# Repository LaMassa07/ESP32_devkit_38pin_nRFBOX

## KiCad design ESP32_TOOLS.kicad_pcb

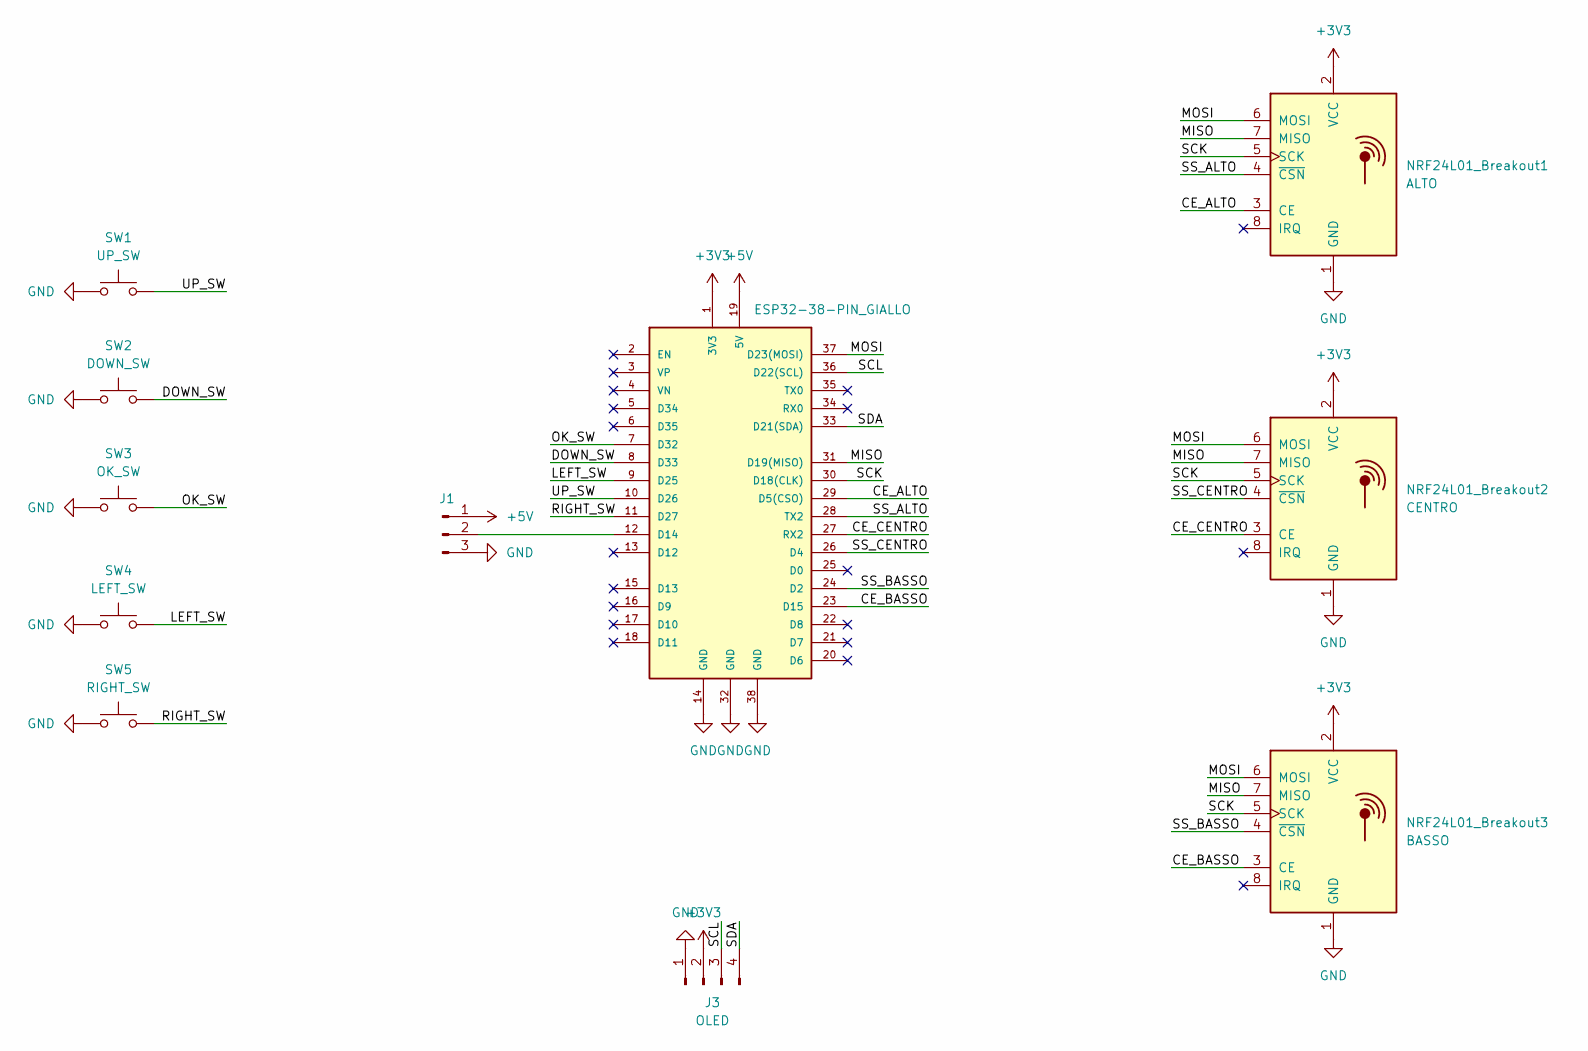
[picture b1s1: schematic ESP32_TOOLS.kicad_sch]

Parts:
J1: LED; PinHeader_1x03_P2.54mm_Vertical
J3: OLED; 128x64OLED
NRF24L01_Breakout1: ALTO; nRF24L01_PA_LNA
NRF24L01_Breakout2: CENTRO; nRF24L01_PA_LNA
NRF24L01_Breakout3: BASSO; nRF24L01_PA_LNA
S1: ESP32-38-PIN_GIALLO; ESP32-38-PIN; PARTREV N/A
SW1: UP_SW; SW_PUSH_6mm_H9.5mm
SW2: DOWN_SW; SW_PUSH_6mm_H9.5mm
SW3: OK_SW; SW_PUSH_6mm_H9.5mm
SW4: LEFT_SW; SW_PUSH_6mm_H9.5mm
SW5: RIGHT_SW; SW_PUSH_6mm_H9.5mm

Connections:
+3V3: J3.2, NRF24L01_Breakout1.2 (VCC), NRF24L01_Breakout2.2 (VCC), NRF24L01_Breakout3.2 (VCC), S1.1 (3V3)
+5V: J1.1, S1.19 (5V)
/CE_ALTO: NRF24L01_Breakout1.3 (CE), S1.29 (D5(CSO))
/CE_BASSO: NRF24L01_Breakout3.3 (CE), S1.23 (D15)
/CE_CENTRO: NRF24L01_Breakout2.3 (CE), S1.27 (RX2)
/DOWN_SW: S1.8 (D33), SW2.2
/LEFT_SW: S1.9 (D25), SW4.2
/MISO: NRF24L01_Breakout1.7 (MISO), NRF24L01_Breakout2.7 (MISO), NRF24L01_Breakout3.7 (MISO), S1.31 (D19(MISO))
/MOSI: NRF24L01_Breakout1.6 (MOSI), NRF24L01_Breakout2.6 (MOSI), NRF24L01_Breakout3.6 (MOSI), S1.37 (D23(MOSI))
/OK_SW: S1.7 (D32), SW3.2
/RIGHT_SW: S1.11 (D27), SW5.2
/SCK: NRF24L01_Breakout1.5 (SCK), NRF24L01_Breakout2.5 (SCK), NRF24L01_Breakout3.5 (SCK), S1.30 (D18(CLK))
/SCL: J3.3, S1.36 (D22(SCL))
/SDA: J3.4, S1.33 (D21(SDA))
/SS_ALTO: NRF24L01_Breakout1.4 (~CSN), S1.28 (TX2)
/SS_BASSO: NRF24L01_Breakout3.4 (~CSN), S1.24 (D2)
/SS_CENTRO: NRF24L01_Breakout2.4 (~CSN), S1.26 (D4)
/UP_SW: S1.10 (D26), SW1.2
GND: J1.3, J3.1, NRF24L01_Breakout1.1 (GND), NRF24L01_Breakout2.1 (GND), NRF24L01_Breakout3.1 (GND), S1.14 (GND), S1.32 (GND), S1.38 (GND), SW1.1, SW2.1, SW3.1, SW4.1, SW5.1
unnamed: J1.2, S1.12 (D14)

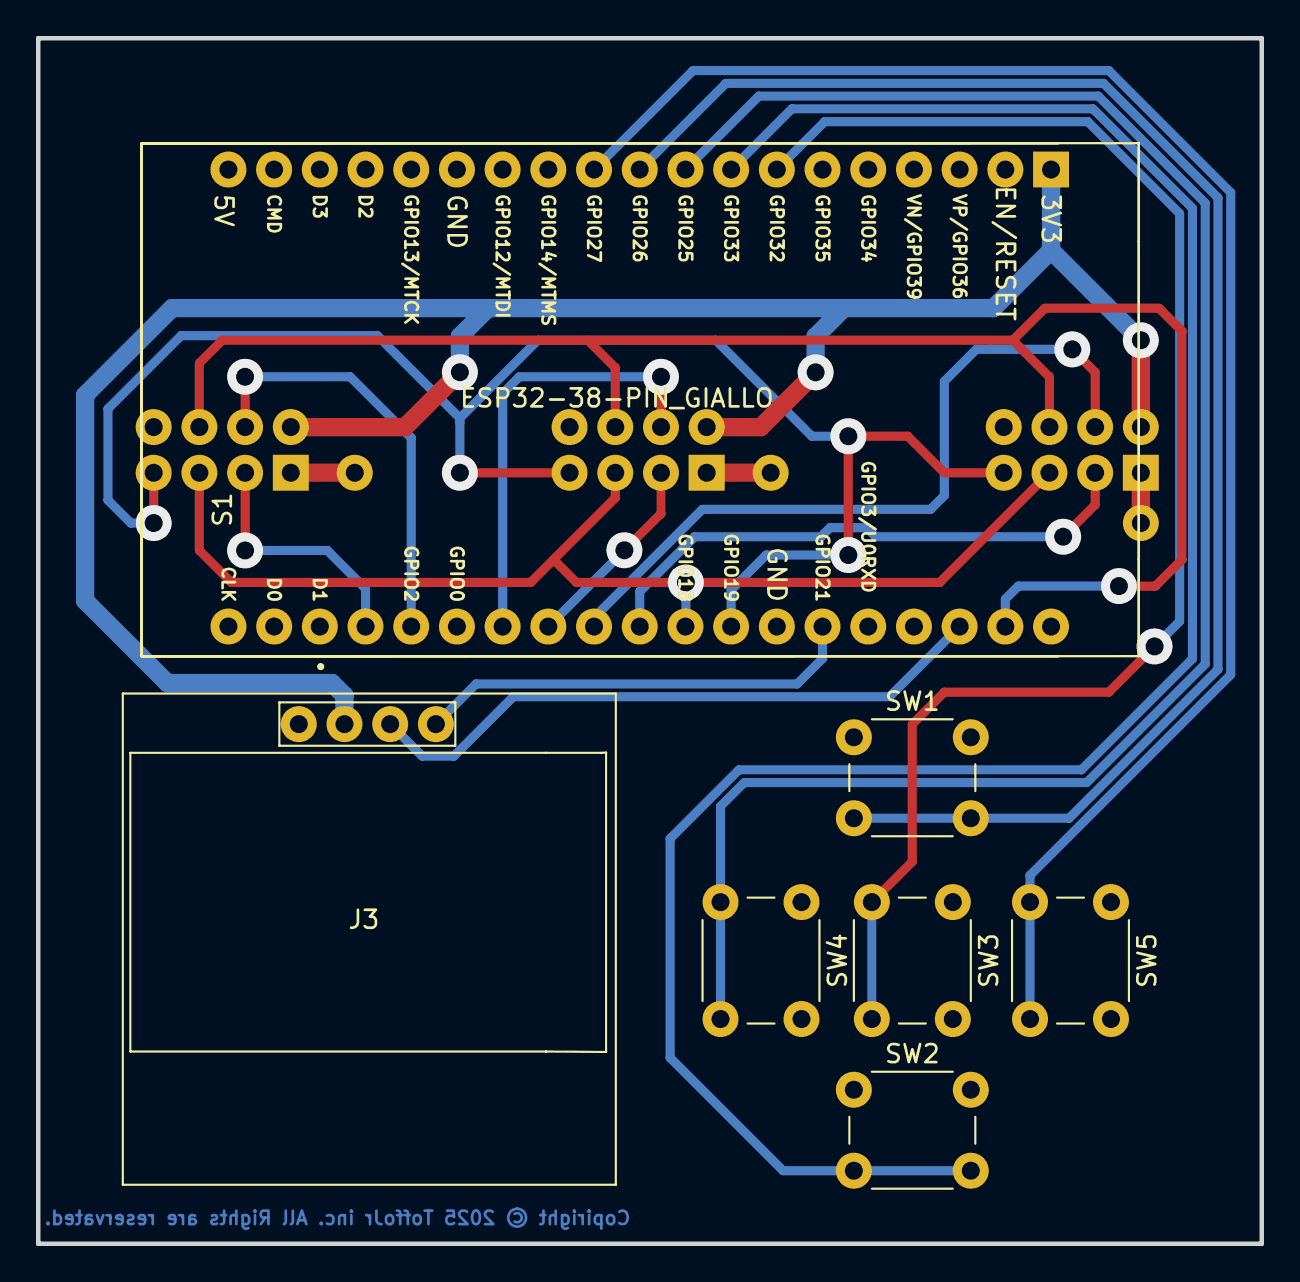
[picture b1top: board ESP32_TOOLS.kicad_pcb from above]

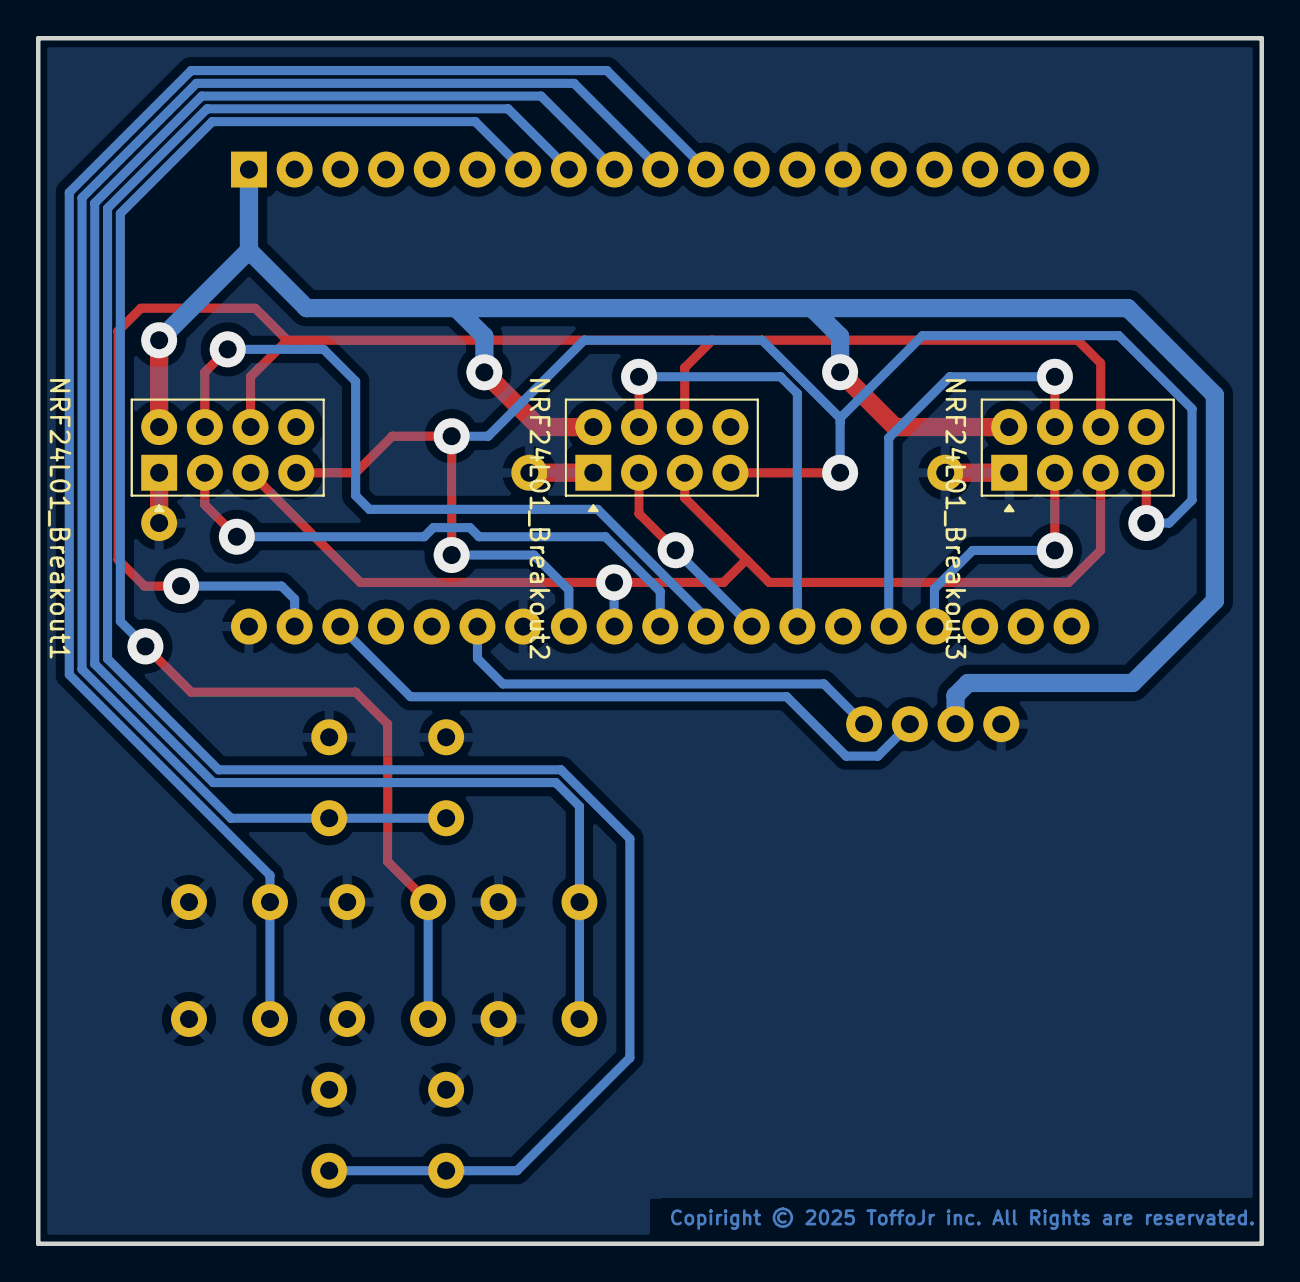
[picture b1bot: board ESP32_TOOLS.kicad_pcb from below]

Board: 2 copper layers, 68.0 x 67.0 mm, 10 parts (3 on the bottom side), 18 nets.

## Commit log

2025-12-04 first
2025-12-04 removed grb
2025-12-04 fofo1
2025-12-09 updated PCB. Complited R1
2025-12-09 small corrections

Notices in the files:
ESP32_TOOLS.kicad_pcb:
Copiright © 2025 ToffoJr inc. All Rights are reservated.
